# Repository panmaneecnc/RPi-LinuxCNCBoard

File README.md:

RPi-LinuxCNCBoard
=================
These files are part of the rpi_rboq project.
driver: Contains all the files related with the HAL(Hardware Abstraction Layer) driver programmed to integrate rpi_rboq to LinuxCNC.
PCB: Contains all the files of the PCB design. To open this files you required Eagle 6.5.0 version, available from: http://www.cadsoftusa.com/
presentation: Contain the presentation designed for oral defense.
raspberry_images: Contains the images compiled during the work using Xenomai and the PREEMPT-RT patch.
report: Contain the full report in PDF format.
testing: Contain all the testing code and libraries written by this work.

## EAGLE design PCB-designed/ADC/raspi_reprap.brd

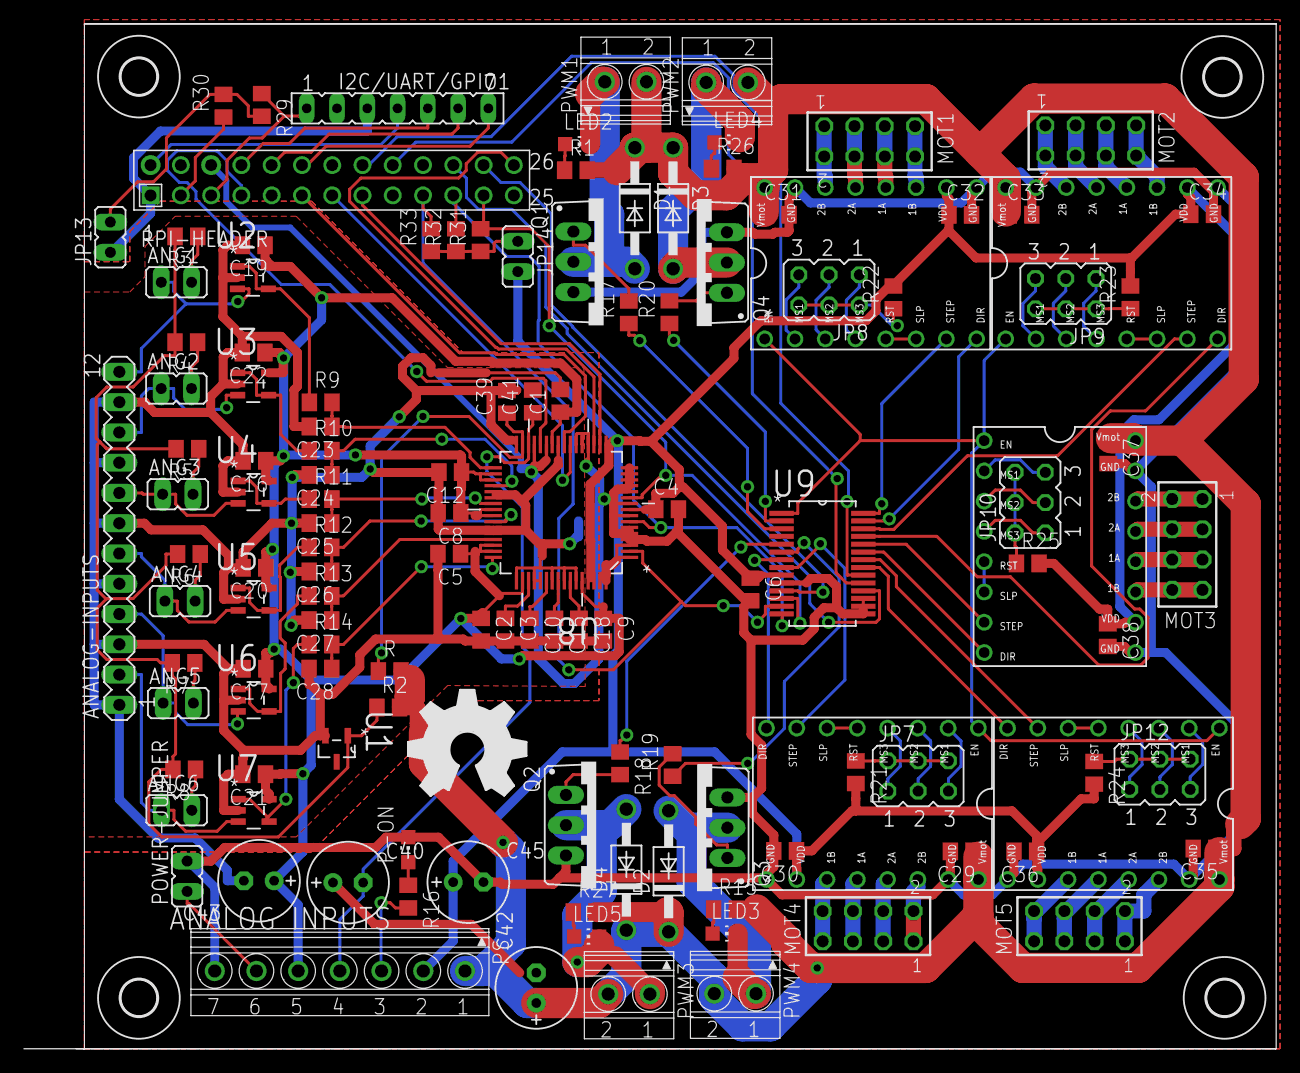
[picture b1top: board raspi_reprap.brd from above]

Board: 2 copper layers, 105.1 x 86.0 mm, 133 parts (1 on the bottom side), 132 nets.

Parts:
ANALOG-INPUTS: MA12-1
ANG1, ANG2, ANG3, ANG4, ANG5, ANG6: JP1
C1, C2, C5, C6, C8, C9, C12, C16, C17, C19, C20, C21, C22, C29, C30, C31, C32, C33, C34, C35, C36, C37, C38, C39, C41: 100nF; C0805
C3: 470nF; C0805
C4: 1uF; C0805
C10, C15, C18: 10uF; C0805
C23, C24, C25, C26, C27, C28: 470pF; C0805
C40, C42, C43, C45: E2,5-7
D1, D2, D3, D4: 1N4004; DO41-10
GROUND_JUCTION: 0; R0805
I2C/UART/GPIO1: FE07
JP7, JP8, JP9, JP10, JP12: JP3Q
JP13, JP14: JP1
LED2, LED3, LED4, LED5: CHIP-LED0805
MOT1, MOT2, MOT3, MOT4, MOT5: TSW-104-02-S-D
P-ON: CHIP-LED0805
POWER-JUMPER: JP1
PS: 1751293
PWM1, PWM2, PWM3, PWM4: +12; 1751248
Q1, Q2, Q3, Q4: TO220BV
R: 0; R0805
R1, R15, R17, R18, R19, R20, R21, R22, R23, R24, R25, R26, R27, R29, R30, R31, R32, R33: 1k; R0805
R2, R16: R0805
R3, R4, R5, R6, R7, R8: 120k; R0805
R9, R10, R11, R12, R13, R14: 43; R0805
RPI-HEADER: RASPBERRY-PI
U1: LM4040D50IDBZR; SOT95P237X112-3N
U2, U3, U4, U5, U6, U7: OPA365AIDBVTG4; SOT95P280X145-5N
U8: ADS8556IPM; QFP50P1200X1200X160-64N
U9: MCP23S17-E/SS; SOP65P780X200-28N
U$2, U$3, U$4, U$5, U$6: A4983CARRIER; A4988BREAKOUT
U$7, U$8, U$9, U$10: 3,0
U$11: OSHW_FILLX350_NOTEXT

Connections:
5VREF: R2.1, R3.2, R4.2, R5.2, R6.2, R7.2, R8.2, U1.1
+3.3V: I2C/UART/GPIO1.3, JP13.1, RPI-HEADER.1
+3V: C4.1, C6.1, C30.1, C32.1, C34.1, C36.1, C38.1, C45.+, JP14.2, PS.2, R21.2, R22.2, R23.2, R24.2, R25.2, U8.9, U8.17, U8.61, U8.62, U9.9, U$2.VDD, U$3.VDD, U$4.VDD, U$5.VDD, U$6.VDD
+5V: C1.1, C2.1, C5.1, C8.1, C9.1, C12.1, C16.1, C17.1, C19.1, C20.1, C21.1, C22.1, C43.+, PS.5, U2.5, U3.5, U4.5, U5.5, U6.5, U7.5, U8.26, U8.34, U8.35, U8.40, U8.41, U8.46, U8.47, U8.50, U8.60
+12IC: C39.1, R.1, U8.31
+12V: C29.1, C31.1, C33.1, C35.1, C37.1, C42.+, D1.C, D2.C, D3.C, D4.C, PS.1, PWM1.2, PWM2.2, PWM3.2, PWM4.2, R.2, R1.2, R2.2, R15.2, R26.2, R27.2, U$2.VMOT, U$3.VMOT, U$4.VMOT, U$5.VMOT, U$6.VMOT
-12V: C40.-, C41.1, PS.4, U8.30
AGND: ANALOG-INPUTS.1, ANALOG-INPUTS.3, ANALOG-INPUTS.5, ANALOG-INPUTS.7, ANALOG-INPUTS.9, ANALOG-INPUTS.11, C1.2, C2.2, C3.2, C5.2, C8.2, C9.2, C10.2, C12.2, C15.2, C16.2, C17.2, C18.2, C19.2, C20.2, C21.2, C22.2, C23.2, C24.2, C25.2, C26.2, C27.2, C28.2, C39.2, C40.+, C41.2, C42.-, C43.-, GROUND_JUCTION.1, U1.2, U2.2, U3.2, U4.2, U5.2, U6.2, U7.2, U8.25, U8.32, U8.37, U8.38, U8.43, U8.44, U8.49, U8.52, U8.53, U8.55, U8.57, U8.59
CE1: RPI-HEADER.24, U9.11
CE2: RPI-HEADER.26, U8.19
CLK: R31.2, RPI-HEADER.23, U8.11, U9.12
ENAMOT: U9.1, U$2.EN, U$3.EN, U$4.EN, U$5.EN, U$6.EN
GND: C4.2, C6.2, C29.2, C30.2, C31.2, C32.2, C33.2, C34.2, C35.2, C36.2, C37.2, C38.2, C45.-, GROUND_JUCTION.2, P-ON.C, POWER-JUMPER.2, PS.7, Q1.S, Q2.S, Q3.S, Q4.S, RPI-HEADER.6, U8.1, U8.3, U8.4, U8.5, U8.6, U8.8, U8.10, U8.12, U8.13, U8.14, U8.15, U8.16, U8.20, U8.21, U8.22, U8.27, U8.29, U8.63, U8.64, U9.10, U9.15, U9.16, U9.17, U$2.GND, U$2.GND@0, U$3.GND, U$3.GND@0, U$4.GND, U$4.GND@0, U$5.GND, U$5.GND@0, U$6.GND, U$6.GND@0
GPIO1: I2C/UART/GPIO1.7, RPI-HEADER.12
M1-MOT2: MOT4.3, MOT4.4, U$2.2A
M1-MOT3: MOT4.5, MOT4.6, U$2.1A
M1-MOT4: MOT4.7, MOT4.8, U$2.1B
M2-MOT1: MOT1.1, MOT1.2, U$3.2B
M2-MOT2: MOT1.3, MOT1.4, U$3.2A
M2-MOT3: MOT1.5, MOT1.6, U$3.1A
M2-MOT4: MOT1.7, MOT1.8, U$3.1B
M3-MOT1: MOT2.1, MOT2.2, U$4.2B
M3-MOT2: MOT2.3, MOT2.4, U$4.2A
M3-MOT3: MOT2.5, MOT2.6, U$4.1A
M3-MOT4: MOT2.7, MOT2.8, U$4.1B
M4-MOT1: MOT5.1, MOT5.2, U$5.2B
M4-MOT2: MOT5.3, MOT5.4, U$5.2A
M4-MOT3: MOT5.5, MOT5.6, U$5.1A
M4-MOT4: MOT5.7, MOT5.8, U$5.1B
M5-MOT1: MOT3.1, MOT3.2, U$6.2B
M5-MOT2: MOT3.3, MOT3.4, U$6.2A
M5-MOT3: MOT3.5, MOT3.6, U$6.1A
M5-MOT4: MOT3.7, MOT3.8, U$6.1B
MISO: R32.2, RPI-HEADER.21, U8.7, U9.14
MOSI: R33.2, RPI-HEADER.19, U8.2, U9.13
MOT4: MOT4.1, MOT4.2, U$2.2B
unnamed: C25.1, R11.2, U8.39
unnamed: ANALOG-INPUTS.8, ANG3.1, U4.3
unnamed: R11.1, U4.1, U4.4
unnamed: ANG3.2, R5.1
unnamed: Q2.G, R18.2
unnamed: C26.1, R12.2, U8.42
unnamed: RPI-HEADER.15, U8.18
unnamed: JP7.3, U$2.MS2
unnamed: U9.21, U$5.DIR
unnamed: P-ON.A, R16.1
unnamed: JP7.1, U$2.MS3
unnamed: Q1.G, R17.2
unnamed: ANALOG-INPUTS.6, ANG4.1, U5.3
unnamed: ANALOG-INPUTS.12, ANG1.1, U2.3
unnamed: R9.1, U2.1, U2.4
unnamed: C23.1, R9.2, U8.33
unnamed: R12.1, U5.1, U5.4
unnamed: ANG1.2, R3.1
unnamed: ANG4.2, R6.1
unnamed: RPI-HEADER.22, U9.18
unnamed: RPI-HEADER.13, U8.23
unnamed: RPI-HEADER.18, U9.19
unnamed: C28.1, R14.2, U8.48
unnamed: C24.1, R10.2, U8.36
unnamed: JP12.5, U$5.MS1
unnamed: Q3.G, R19.2
unnamed: JP10.5, U$6.MS1
unnamed: JP9.5, U$4.MS1
unnamed: JP8.2, JP8.4, JP8.6, R22.1
unnamed: JP7.2, JP7.4, JP7.6, R21.1
unnamed: JP12.3, U$5.MS2
unnamed: JP12.1, U$5.MS3
unnamed: U9.22, U$5.STEP
unnamed: R20.1, U9.2
unnamed: U$2.RST, U$2.SLP
unnamed: RPI-HEADER.16, U9.20
unnamed: R17.1, U9.3
unnamed: R18.1, U9.5
unnamed: JP8.5, U$3.MS1
unnamed: RPI-HEADER.7, U8.28
unnamed: JP8.3, U$3.MS2
unnamed: JP8.1, U$3.MS3
unnamed: JP9.3, U$4.MS2
unnamed: U9.23, U$6.DIR
unnamed: U9.24, U$6.STEP
unnamed: U$3.RST, U$3.SLP
unnamed: Q4.G, R20.2
unnamed: JP9.1, U$4.MS3
unnamed: JP10.3, U$6.MS2
unnamed: JP10.1, U$6.MS3
unnamed: JP7.5, U$2.MS1
unnamed: LED2.A, R1.1
unnamed: LED5.A, R27.1
unnamed: JP9.2, JP9.4, JP9.6, R23.1
unnamed: JP13.2, R29.2, R30.2
unnamed: LED3.A, R15.1
unnamed: U9.25, U$4.DIR
unnamed: U9.26, U$4.STEP
unnamed: U$4.RST, U$4.SLP
unnamed: I2C/UART/GPIO1.6, RPI-HEADER.10
unnamed: LED4.A, R26.1
unnamed: I2C/UART/GPIO1.5, RPI-HEADER.8
unnamed: I2C/UART/GPIO1.4, RPI-HEADER.2
unnamed: R30.1, RPI-HEADER.3
unnamed: I2C/UART/GPIO1.1, R29.1, RPI-HEADER.5
unnamed: JP12.2, JP12.4, JP12.6, R24.1
unnamed: U9.27, U$3.DIR
unnamed: U9.28, U$3.STEP
unnamed: U$5.RST, U$5.SLP
unnamed: ANALOG-INPUTS.10, ANG2.1, U3.3
unnamed: JP14.1, R31.1, R32.1, R33.1
unnamed: R10.1, U3.1, U3.4
unnamed: ANG2.2, R4.1
unnamed: R19.1, U9.6
unnamed: C27.1, R13.2, U8.45
unnamed: ANALOG-INPUTS.4, ANG5.1, U6.3
unnamed: U9.7, U$2.DIR
unnamed: U9.8, U$2.STEP
unnamed: JP10.2, JP10.4, JP10.6, R25.1
unnamed: U$6.RST, U$6.SLP
unnamed: R13.1, U6.1, U6.4
unnamed: ANG5.2, R7.1
unnamed: ANALOG-INPUTS.2, ANG6.1, U7.3
unnamed: R14.1, U7.1, U7.4
unnamed: ANG6.2, R8.1
unnamed: RPI-HEADER.11, U8.24
POK: PS.3, R16.2
PON: POWER-JUMPER.1, PS.6
PWM1: D4.A, LED5.C, PWM3.1, Q2.D
PWM2: D1.A, LED2.C, PWM1.1, Q1.D
PWM3: D2.A, LED3.C, PWM4.1, Q3.D
PWM4: D3.A, LED4.C, PWM2.1, Q4.D
REFC_A: C10.1, U8.54
REFC_B: C15.1, U8.56
REFC_C: C18.1, U8.58
REFIO: C3.1, U8.51

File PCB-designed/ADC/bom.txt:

Partlist exported from C:/Users/rboq/Documents/eagle/ADC/raspi_reprap.sch at 12/2/2013 4:26:29 PM

Qty Value          Device           Package                 Parts                                               Description                                               
6                  JP1E             JP1                     JP1, JP2, JP3, JP4, JP5, JP6                        JUMPER                                                    
5                  JP2Q             JP2Q                    JP7, JP8, JP9, JP10, JP11                           JUMPER                                                    
1                  LEDCHIP-LED0805  CHIP-LED0805            LED1                                                LED                                                       
4                  PMOSFET_NTO220BV TO220BV                 Q1, Q2, Q3, Q4                                      Power MOSFET N-Channel                                    
2                  R-EU_R0805       R0805                   R2, R16                                             RESISTOR, European symbol                                 
4   +12            1751248          1751248                 TM, TM1, TM2, TM3                                   MKDS 1/ 2-3,5 Printklemme                                 
1   0              R-EU_R0805       R0805                   C13                                                 RESISTOR, European symbol                                 
12  100nF          C-EUC0201        C0201                   C1, C2, C5, C6, C7, C8, C9, C11, C12, C14, C39, C41 CAPACITOR, European symbol                                
6   100nF          C-EUC0402        C0402                   C16, C17, C19, C20, C21, C22                        CAPACITOR, European symbol                                
10  100nF          C-EUC0805        C0805                   C29, C30, C31, C32, C33, C34, C35, C36, C37, C38    CAPACITOR, European symbol                                
3   10uF           C-EUC0201        C0201                   C10, C15, C18                                       CAPACITOR, European symbol                                
4   10uF           C-EUC0805        C0805                   C40, C42, C43, C44                                  CAPACITOR, European symbol                                
6   120k           R-EU_R0805       R0805                   R3, R4, R5, R6, R7, R8                              RESISTOR, European symbol                                 
6   1751248        1751248          1751248                 ANG1, ANG2, ANG3, ANG4, ANG5, ANG6                  MKDS 1/ 2-3,5 Printklemme                                 
5   1751264        1751264          1751264                 X2, X3, X4, X5, X6                                  MKDS 1/ 4-3,5 Printklemme                                 
1   1751293        1751293          1751293                 X1                                                  MKDS 1/ 7-3,5 Printklemme                                 
9   1k             R-EU_R0805       R0805                   R17, R18, R19, R20, R21, R22, R23, R24, R25         RESISTOR, European symbol                                 
1   1uF            C-EUC0201        C0201                   C4                                                  CAPACITOR, European symbol                                
6   43             R-EU_R0805       R0805                   R9, R10, R11, R12, R13, R14                         RESISTOR, European symbol                                 
1   470nF          C-EUC0201        C0201                   C3                                                  CAPACITOR, European symbol                                
6   470pF          C-EUC0805        C0805                   C23, C24, C25, C26, C27, C28                        CAPACITOR, European symbol                                
5   A4983CARRIER   A4983CARRIER     A4988BREAKOUT           U$2, U$3, U$4, U$5, U$6                                                                                       
1   ADS8556IPM     ADS8556IPM       QFP50P1200X1200X160-64N U8                                                  ANALOG-TO-DIGITAL CONVERTERS                              
1   LM4040D50IDBZR LM4040D50IDBZR   SOT95P237X112-3N        U1                                                  PRECISION MICROPOWER SHUNT VOLTAGE REFERENCE              
1   MCP23S17-E/SS  MCP23S17-E/SS    SOP65P780X200-28N       U9                                                  IC, 16-Bit I/O Expander with Serial Interface,    SSOP-28 
6   OPA365AIDBVTG4 OPA365AIDBVTG4   SOT95P280X145-5N        U2, U3, U4, U5, U6, U7                              OPERATIONAL AMPLIFIER                                     
1   RASPBERRY-PI   RASPBERRY-PI     RASPBERRY-PI            U$1                                                 Raspberry Pi Board                                        
4   TPB1,27        TPB1,27          B1,27                   TP1, TP2, TP3, TP4                                  Test pad

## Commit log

2014-05-10 First commit
    Preliminary version
2014-05-13 Signal names changes
    I change the signals names
2014-05-13 value clock
    value
2014-05-13 commit test
    Test commit
2014-05-14 Make
    xeno make
2014-05-17 new version of driverr
    this version works perfecly with hal_meter and halscope
2014-05-17 works
    Driver works, perfectly and we upgrade just part of the register
2014-05-18 Revert "mal"
    This reverts commit d0d7f311fbdab2fbcf77bb7ca951dadb8a9a1e92.
2014-05-27 Final commit
    All documentation included presentation and report
2014-05-30 Organized
    New organization
2014-05-30 New version
2014-06-29 New order
    New order
